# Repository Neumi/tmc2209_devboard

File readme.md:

# TMC2209 Development Board for Arduino Uno
A development board to test the Trinamic TMC2209 stepper motor controller on an Arduino Uno.

This board should cover all options and IOs that Trinamic provides for its TMC2209.

Facts:
 - All TMC2209 pins are connected to digital pins of the Arduino. 
 - XT30 power connector
 - voltage source selector Arduino VIN or XT30
 - TVS diodes on 5v and 28V lane of the TMC2209
 - different wiring schemes for the JST motor connector (because getting the right phases is not easy apparently!)
 - different current setting selectable with solder bridges (or custom resistor also possible)
 - motor voltage sensing via voltage divider on A0
 - reset button for Arudino + power LED

KICAD and production files for JLCPCB are also included. Code will follow. 
Production cost incl assembly is around 50€ for 5pcs. THT components not included.

Feedback is very welcome!

## Video:

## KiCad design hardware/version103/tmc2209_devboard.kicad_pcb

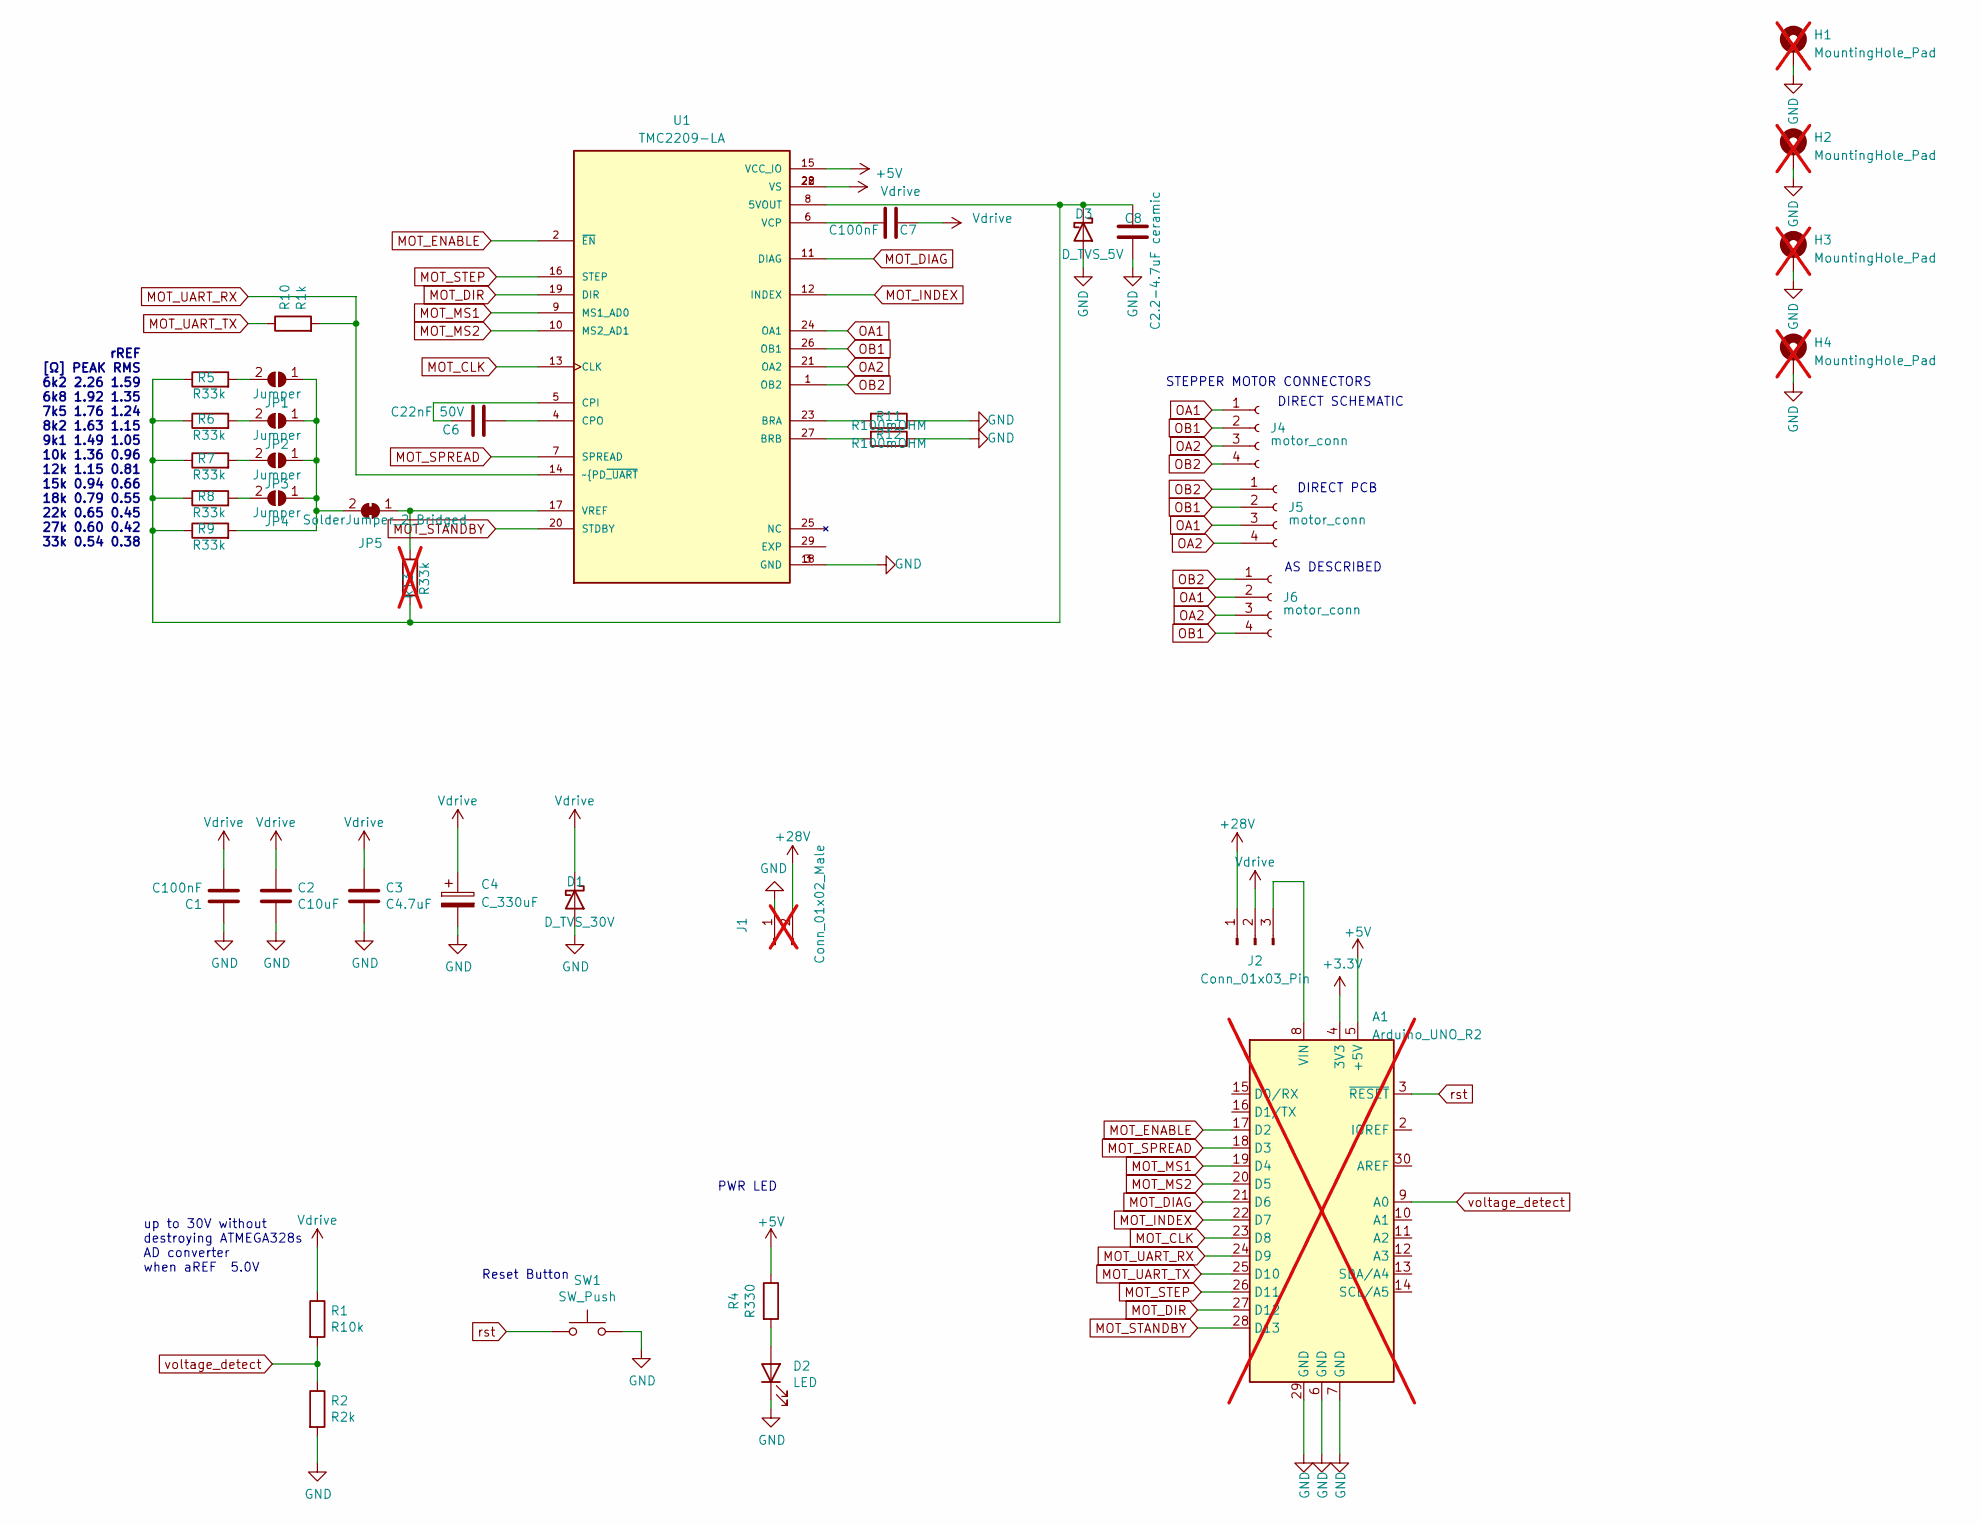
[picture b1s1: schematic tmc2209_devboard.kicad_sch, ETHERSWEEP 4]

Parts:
A1: Arduino_UNO_R2; Arduino_UNO_R2_WithMountingHoles; not fitted
C1, C7: C100nF; C_0805_2012Metric; LCSC C49678
C2: C10uF; C_1206_3216Metric; LCSC C13585
C3: C4.7uF; C_1206_3216Metric; LCSC C29823
C4: C_330uF; CP_Elec_10x10; LCSC C249985
C6: C22nF 50V; C_0805_2012Metric; LCSC C1729
C8: C2.2-4.7uF ceramic; C_1206_3216Metric; LCSC C29823
D1: D_TVS_30V; D_SOD-123; LCSC C553410
D2: LED; LED_0805_2012Metric; LCSC C84256
D3: D_TVS_5V; D_SOD-123; LCSC C478011
H1, H2, H3, H4: MountingHole_Pad; MountingHole_3.2mm_M3_Pad_Via; not fitted
J1: Conn_01x02_Male; AMASS_XT30PW-M_1x02_P2.50mm_Horizontal; LCSC C431092; not fitted
J2: Conn_01x03_Pin; PinHeader_1x03_P2.54mm_Vertical
J4, J5, J6: motor_conn; JST_EH_S4B-EH_1x04_P2.50mm_Horizontal
JP1, JP2, JP3, JP4: Jumper; SolderJumper-2_P1.3mm_Open_RoundedPad1.0x1.5mm
JP5: SolderJumper_2_Bridged; SolderJumper-2_P1.3mm_Bridged_RoundedPad1.0x1.5mm
R1: R10k; R_0805_2012Metric; LCSC C3016734
R2: R2k; R_0805_2012Metric; LCSC C17604
R4: R330; R_0805_2012Metric; LCSC C17630
R5, R6, R7, R8, R9: R33k; R_0805_2012Metric; LCSC C17633
R10: R1k; R_0805_2012Metric; LCSC C17513
R11, R12: R100mOHM; R_2010_5025Metric; LCSC C175979
R13: R33k; R_0805_2012Metric; LCSC C17633; not fitted
SW1: SW_Push; SW_Push_1P1T_NO_CK_KSC6xxJ; LCSC C318884
U1: TMC2209-LA; QFN50P500X500X90-29N; PARTREV 1.08; LCSC C465949

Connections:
+3V3: A1.4 (3V3)
+5V: A1.5 (+5V), R4.1, U1.15 (VCC_IO)
+28V: J1.2, J2.1
GND: A1.6 (GND), A1.7 (GND), A1.29 (GND), C1.1, C2.2, C3.2, C4.2, C8.2, D1.2 (A), D2.1 (K), D3.2 (A), H1.1, H2.1, H3.1, H4.1, J1.1, R2.2, R11.1, R12.1, SW1.2, U1.3 (GND), U1.18 (GND)
MOT_CLK: A1.23 (D8), U1.13 (CLK)
MOT_DIAG: A1.21 (D6), U1.11 (DIAG)
MOT_DIR: A1.27 (D12), U1.19 (DIR)
MOT_ENABLE: A1.17 (D2), U1.2 (~EN)
MOT_INDEX: A1.22 (D7), U1.12 (INDEX)
MOT_MS1: A1.19 (D4), U1.9 (MS1_AD0)
MOT_MS2: A1.20 (D5), U1.10 (MS2_AD1)
MOT_SPREAD: A1.18 (D3), U1.7 (SPREAD)
MOT_STANDBY: A1.28 (D13), U1.20 (STDBY)
MOT_STEP: A1.26 (D11), U1.16 (STEP)
MOT_UART_RX: A1.24 (D9), R10.2, U1.14 (~PD~{_UART)
MOT_UART_TX: A1.25 (D10), R10.1
unnamed: A1.8 (VIN), J2.3
unnamed: D2.2 (A), R4.2
unnamed: C8.1, D3.1 (K), R5.1, R6.1, R7.1, R8.1, R9.1, R13.1, U1.8 (5VOUT)
unnamed: JP1.1 (A), JP2.1 (A), JP3.1 (A), JP4.1 (A), JP5.2 (B), R9.2
unnamed: JP1.2 (B), R5.2
unnamed: JP2.2 (B), R6.2
unnamed: JP3.2 (B), R7.2
unnamed: JP4.2 (B), R8.2
unnamed: JP5.1 (A), R13.2, U1.17 (VREF)
unnamed: R11.2, U1.23 (BRA)
unnamed: R12.2, U1.27 (BRB)
unnamed: C6.1, U1.5 (CPI)
unnamed: C6.2, U1.4 (CPO)
unnamed: C7.1, U1.6 (VCP)
OA1: J4.1, J5.3, J6.2, U1.24 (OA1)
OA2: J4.3, J5.4, J6.3, U1.21 (OA2)
OB1: J4.2, J5.2, J6.4, U1.26 (OB1)
OB2: J4.4, J5.1, J6.1, U1.1 (OB2)
Vdrive: C1.2, C2.1, C3.1, C4.1, C7.2, D1.1 (K), J2.2, R1.1, U1.22 (VS), U1.28 (VS)
rst: A1.3 (~RESET), SW1.1
voltage_detect: A1.9 (A0), R1.2, R2.1

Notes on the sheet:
STEPPER MOTOR CONNECTORS
DIRECT SCHEMATIC
AS DESCRIBED
PWR LED
up to 30V without destroying ATMEGA328s AD converter when aREF 5.0V
rREF [Ω] PEAK RMS 6k2 2.26 1.59 6k8 1.92 1.35 7k5 1.76 1.24 8k2 1.63 1.15 9k1 1.49 1.05 10k 1.36 0.96 12k 1.15 0.81 15k 0.94 0.66 18k 0.79 0.55 22k 0.65 0.45 27k 0.60 0.42 33k 0.54 0.38
DIRECT PCB
Reset Button

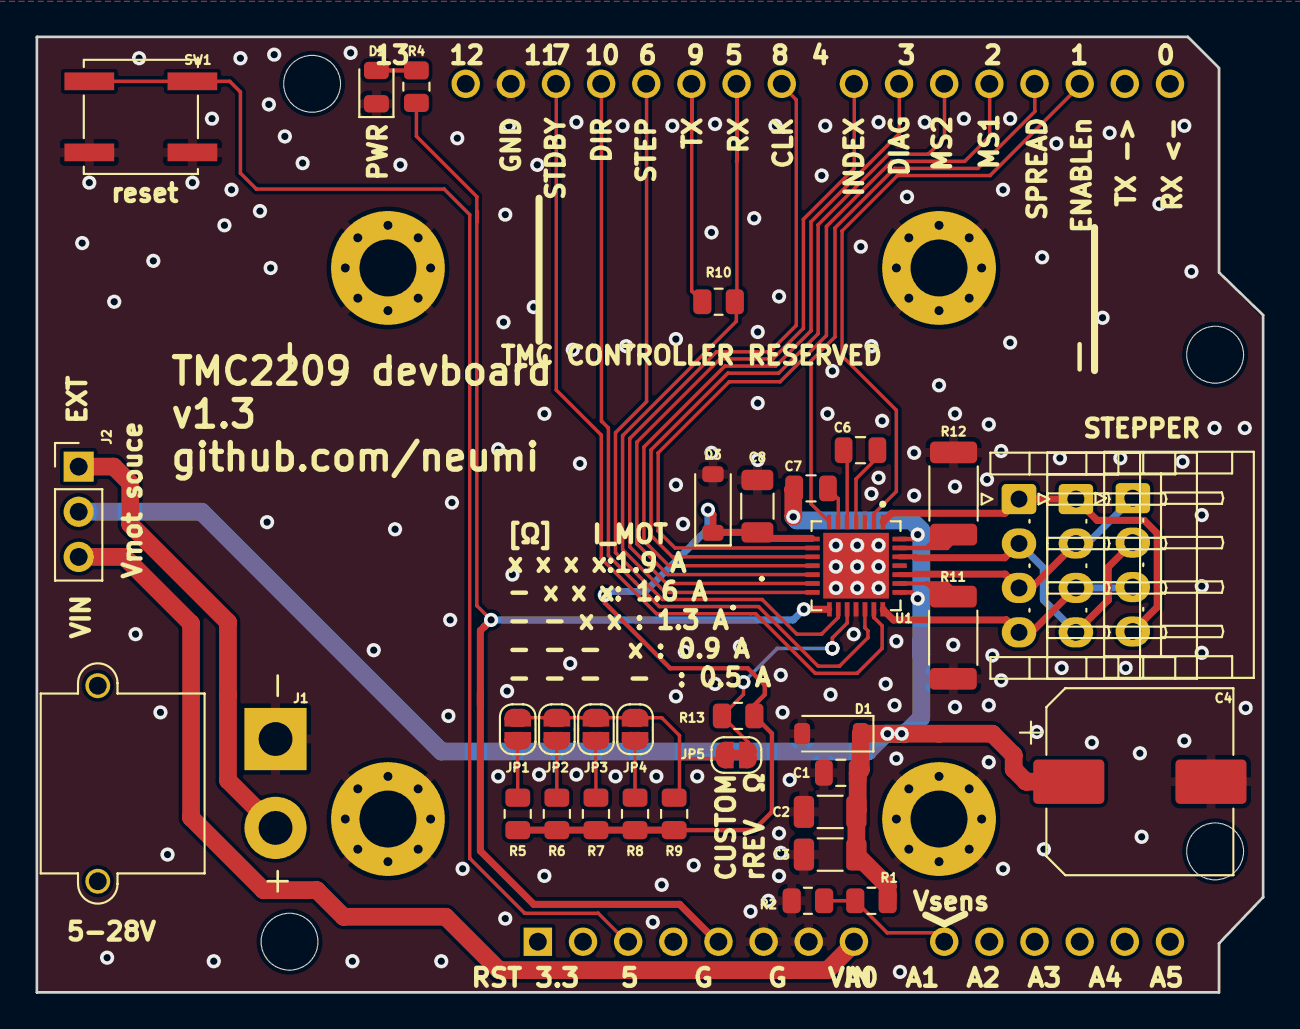
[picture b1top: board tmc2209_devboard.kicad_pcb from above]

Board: 2 copper layers, 69.0 x 53.8 mm, 39 parts (1 on the bottom side), 36 nets.

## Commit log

2023-03-13 initial commit. version 1.0 production ready
2023-03-13 Update readme.md
    added readme
2023-03-13 added version 102, added nema17 mount and fixed switched vin text
2023-03-13 fixed order files and added images
2023-03-13 corrected file name
2023-03-13 Update readme.md
    added order_layout.png
2023-03-13 added 3d files and perspective renderings
2023-03-13 Update readme.md
    assed perspective images
2023-03-26 added photos of manufactured v1.2 boarsds
2023-03-26 minor changed for version 1.3. Changed component number for JLC parts for R3 (was wrong) relates #3
2023-03-26 added HW version 1.3
2023-03-26 Update readme.md
    added photos of finished 1.2 board
2023-03-27 added example code
2023-03-28 Create FUNDING.yml
    added sponsoring button
2023-03-29 changed motor power source connector and elec cap for lower nema17 placement. Added production files for 103
2023-03-29 added gnd connection to motor mounts, added DNP for static PCB footprints
2023-03-30 Update readme.md
    added video to readme
2023-04-23 minor
2023-04-23 added images
2023-04-23 minor design changes, added produciton files for version 103
